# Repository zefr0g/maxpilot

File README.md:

# MaxPilot

> Pilotez vos radiateurs électriques en WiFi depuis Home Assistant — carte open-source, ~12 € de composants, 100 % local.

[English version → README.en.md](README.en.md)

| Carte assemblée | Boîtier imprimé en 3D |
|:--:|:--:|
|  |  |

MaxPilot est une carte open-source qui se branche sur le **fil pilote** de vos radiateurs électriques et commande leur mode (Confort, Éco, Hors-gel, Arrêt) depuis Home Assistant, via ESPHome. Plus besoin de programmateur mural : la carte remplace le thermostat central, sans cloud ni abonnement. Elle est conçue autour de composants **peu coûteux et faciles à trouver** (WeMos D1 Mini, optocoupleurs, alimentation HLK-PM01) et se soude entièrement en traversant : accessible à tout amateur d'électronique.

## Pourquoi MaxPilot ?

- **Local et ouvert** — pas de cloud, pas d'application propriétaire : ESPHome + Home Assistant, et vous gardez le contrôle
- **Vraiment pas cher** — ~12 € par radiateur, tout compris (voir [le coût](#coût))
- **Un fil pilote, plusieurs radiateurs** — une carte pilote tous les radiateurs raccordés au même fil pilote
- **Thermostat intégré** — importez n'importe quel capteur de température de Home Assistant et laissez la carte réguler
- **Conçu pour le 230 V** — fusible, varistance, alimentation isolée, distances d'isolement IPC-2221B / IEC 62368-1, boîtier fermé
- **Tout est fourni** — schéma et PCB KiCad, Gerbers, nomenclature, firmware, boîtier OpenSCAD/STL

| | MaxPilot | Module WiFi du commerce (ex. Heatzy Pilote) | Module Z-Wave (ex. Qubino Fil Pilote) |
|---|:--:|:--:|:--:|
| Prix indicatif par radiateur | **~12 €** | ~50 € | ~60 € |
| Fonctionne sans cloud | ✅ | ❌ | ✅ |
| Intégration Home Assistant | native (ESPHome) | via intégration tierce | via Z-Wave JS + clé USB |
| Firmware modifiable | ✅ | ❌ | ❌ |
| Matériel ouvert | ✅ | ❌ | ❌ |
| Montage à faire soi-même | oui (soudure traversante) | non | non |

---

## Sommaire

- [C'est quoi le fil pilote ?](#cest-quoi-le-fil-pilote-)
- [Fonctionnalités](#fonctionnalités)
- [Coût](#coût)
- [Démarrage rapide](#démarrage-rapide)
- [Câblage](#câblage)
- [Schéma](#schéma)
- [Nomenclature](#nomenclature)
- [Firmware ESPHome](#firmware-esphome)
- [Intégration Home Assistant](#intégration-home-assistant)
- [Fabrication du PCB](#fabrication-du-pcb)
- [Boîtier](#boîtier)
- [Sécurité](#sécurité)
- [Contribuer](#contribuer)
- [Licence](#licence)

---

## C'est quoi le fil pilote ?

Le **fil pilote** est le système normalisé en France (protocole GIFAM) pour piloter les radiateurs électriques. En plus de la phase et du neutre, un fil supplémentaire — le fil pilote — transporte un signal de commande dérivé du 230 V. Le radiateur choisit son mode selon la **forme du signal** qu'il reçoit :

| Mode | Ce que fait le radiateur | Signal sur le fil pilote | SSR1 | SSR2 |
|---|---|---|:---:|:---:|
| **Confort** | Chauffe à la température du thermostat | Pas de signal (fil ouvert) | OFF | OFF |
| **Éco** | Réduit la consigne de ~3-4 °C | Sinusoïde complète 230 V | ON | ON |
| **Hors-gel** | Maintient ~7 °C minimum | Alternance négative uniquement | ON | OFF |
| **Arrêt** | Radiateur éteint | Alternance positive uniquement | OFF | ON |

```
Confort (pas de signal)            Éco (sinusoïde complète)

                                        ╭──╮      ╭──╮
                                       ╱    ╲    ╱    ╲
 ──────────────────────        ───────╱──────╲──╱──────╲───
                                    ╲    ╱    ╲    ╱
                                     ╰──╯      ╰──╯

   SSR1: OFF  SSR2: OFF           SSR1: ON   SSR2: ON

Hors-gel (alternance −)            Arrêt (alternance +)

                                        ╭──╮      ╭──╮
                                       ╱    ╲    ╱    ╲
 ───────────────────────────       ────╱──────╲──╱──────╲───
    ╲    ╱    ╲    ╱
     ╰──╯      ╰──╯

   SSR1: ON   SSR2: OFF           SSR1: OFF  SSR2: ON
```

MaxPilot utilise **deux optocoupleurs triac MOC3041M** (SSR1 et SSR2), chacun en série avec une **diode 1N4007** montée en sens opposé. SSR1 laisse passer l'alternance négative, SSR2 l'alternance positive ; les deux ensemble donnent la sinusoïde complète. Les MOC3041M commutent au passage par zéro, donc sans parasites. Le fil pilote ne consomme que quelques milliampères : une seule carte peut piloter **tous les radiateurs raccordés au même fil pilote**.

---

## Fonctionnalités

- ESP8266 (WeMos D1 Mini) avec WiFi intégré, firmware ESPHome
- Sélecteur de mode Confort / Éco / Hors-gel / Arrêt dans Home Assistant
- Thermostat optionnel : capteur de température importé depuis Home Assistant, presets Confort / Éco / Hors-gel / Absent
- Mode restauré après coupure de courant
- Alimentation AC/DC isolée (HLK-PM01, 5 V), fusible 1 A, varistance 275 V
- Optocoupleurs à passage par zéro (MOC3041M)
- PCB 99 × 38 mm, composants traversants uniquement, 4 trous de fixation M2
- Boîtier imprimable en 3D (OpenSCAD + STL) avec aération au-dessus de l'alimentation

---

## Coût

Prix indicatifs 2026 (AliExpress / LCSC / grossistes, hors port), pour une carte :

| Composant | Prix approx. |
|---|--:|
| WeMos D1 Mini | 3,00 € |
| HLK-PM01 | 3,00 € |
| 2 × MOC3041M | 1,20 € |
| Bornier 7,62 mm | 0,70 € |
| Porte-fusible + fusible 1 A | 0,80 € |
| Varistance, diodes, résistances, condensateur | 0,60 € |
| PCB (JLCPCB, lot de 5) | ~2,00 € |
| **Total** | **~11 €** |

---

## Démarrage rapide

1. **Commander le PCB** — envoyez `hardware/gerber/MaxPilot.zip` à JLCPCB, PCBWay, Aisler…
2. **Souder les composants** — voir la [nomenclature](#nomenclature) ; tout est traversant
3. **Flasher le firmware** — branchez le D1 Mini en USB et lancez `esphome run esphome/maxpilot_ch1.yaml` (voir [Firmware ESPHome](#firmware-esphome))
4. **Câbler la carte** — phase, neutre et fil pilote sur le bornier, courant coupé (voir [câblage](#câblage))
5. **Fermer le boîtier** — indispensable, la carte est au 230 V
6. **Ajouter à Home Assistant** — le périphérique est détecté automatiquement par l'intégration ESPHome
7. **Piloter vos radiateurs** — depuis le tableau de bord, des automatisations ou le thermostat

---

## Câblage

> ⚠️ **ATTENTION** : coupez le courant au disjoncteur avant tout câblage et vérifiez l'absence de tension.

La carte se branche sur le bornier 3 points (J1). Le fil pilote de votre radiateur est le fil noir (parfois gris) qui sort du radiateur à côté de la phase et du neutre. Il ne doit **jamais** être raccordé au neutre ni à la terre.

```
                    Bornier J1
                   ┌─────┬─────┬─────┐
                   │  L  │  N  │  P  │
                   └──┬──┴──┬──┴──┬──┘
                      │     │     │
                      │     │     └──── Fil pilote vers le(s) radiateur(s)
                      │     │
                      │     └────────── Neutre (bleu)
                      │
                      └──────────────── Phase (marron ou rouge)

          Depuis le tableau électrique (circuit des radiateurs)
```

Alimentez la carte depuis le **même circuit** que les radiateurs qu'elle pilote : le signal fil pilote est référencé au neutre du radiateur.

---

## Schéma

Le schéma complet est dans `hardware/kicad/MaxPilot.kicad_sch` (KiCad 9).

### Architecture

```
Secteur ──► F1 (fusible 1 A) ──► RV1 (varistance) ──► PS1 (HLK-PM01) ──► 5 V
   │                                                          │
   │                                                   U1 (WeMos D1 Mini)
   │                                                    │            │
   │                                                GPIO D3      GPIO D7
   │                                                    │            │
   │                                                R1 (570 Ω)   R2 (570 Ω)
   │                                                    │            │
   ├──────────────────────────────────────────── U2 (MOC3041M)  U3 (MOC3041M)
   │  phase                                            │            │
   │                                               D1 (1N4007)  D2 (1N4007)
   │                                               alternance −  alternance +
   │                                                    └─────┬──────┘
   │                                                          ▼
   └───────────────────────────────────────────────►  P (fil pilote)
```

Les deux optocoupleurs sont branchés en parallèle entre la phase et le fil pilote, chacun à travers sa diode. La partie basse tension (5 V, ESP8266) est isolée du secteur par l'alimentation HLK-PM01 et par les optocoupleurs.

### Brochage

| GPIO | Fonction |
|------|----------|
| D3 (GPIO0)  | SSR1 — U2 + D1, alternance négative (Hors-gel, Éco) |
| D7 (GPIO13) | SSR2 — U3 + D2, alternance positive (Arrêt, Éco) |

Les GPIO commandent la LED des optocoupleurs en logique inversée (niveau bas = allumé). D3 étant une broche de démarrage de l'ESP8266, elle reste haute au boot : le radiateur n'est jamais commuté pendant le démarrage.

---

## Nomenclature

| Réf | Qté | Valeur | Description |
|-----|:---:|--------|-------------|
| U1 | 1 | WeMos D1 Mini | Microcontrôleur ESP8266 |
| PS1 | 1 | HLK-PM01 | Alimentation AC/DC 5 V isolée |
| U2, U3 | 2 | MOC3041M | Optocoupleur triac à passage par zéro, DIP-6 — **couper la broche 5 avant soudure** |
| D1, D2 | 2 | 1N4007 | Diodes de sélection d'alternance |
| R1, R2 | 2 | 560–570 Ω | Résistances axiales (limitation LED des optos) |
| C1 | 1 | 22 µF 25 V | Condensateur céramique de découplage 5 V |
| F1 | 1 | 1 A | Fusible lame mini + porte-fusible Keystone 3568 |
| RV1 | 1 | 14D431K | Varistance 275 V AC |
| J1 | 1 | 3 pts, pas 7,62 mm | Bornier à vis, ex. Würth 691311400103, Phoenix MKDS 1,5/3-7,62 |

La nomenclature exportée de KiCad est dans `hardware/MaxPilot.csv`.

---

## Firmware ESPHome

Le firmware est une configuration ESPHome pure, sans code custom.

```
esphome/
├── maxpilot_ch1.yaml                   # une carte = un fichier (nom, broches, secrets)
├── maxpilot_ch1_with_temp.yaml.example # variante avec thermostat
├── secrets.yaml.example
└── common/
    ├── core.yaml             # carte, API, OTA, WiFi de secours, diagnostics
    ├── maxpilot.yaml         # logique fil pilote (SSR + sélecteur de mode)
    └── maxpilot_climate.yaml # thermostat optionnel
```

### 1. Secrets

```bash
cp esphome/secrets.yaml.example esphome/secrets.yaml
# Éditez esphome/secrets.yaml : WiFi et clé de chiffrement API (openssl rand -base64 32)
```

### 2. Flasher

```bash
# Premier flash (D1 Mini branché en USB)
esphome run esphome/maxpilot_ch1.yaml

# Mises à jour suivantes en OTA
esphome run esphome/maxpilot_ch1.yaml --device maxpilot-ch1.local
```

Pour une deuxième carte, copiez `maxpilot_ch1.yaml` et changez `name` et `ch_name`.

### 3. Thermostat (optionnel)

Si un capteur de température de la pièce existe dans Home Assistant (Zigbee, BLE, autre ESPHome…), la carte peut réguler elle-même. Voir `esphome/maxpilot_ch1_with_temp.yaml.example` :

```yaml
substitutions:
  temp_sensor_entity: "sensor.temperature_salon"   # votre capteur dans Home Assistant

packages:
  core: !include common/core.yaml
  maxpilot: !include common/maxpilot.yaml
  climate: !include common/maxpilot_climate.yaml
```

| Preset | Consigne | Fil pilote |
|--------|:--------:|-----------------|
| **Confort** | 19 °C | Confort quand il fait froid, Éco une fois la consigne atteinte |
| **Éco** | 17 °C | idem, autour de 17 °C |
| **Hors-gel** | 7 °C | idem, autour de 7 °C |
| **Absent** | — | Arrêt |

Le thermostat agit toujours à travers le sélecteur de mode : l'état affiché dans Home Assistant est celui réellement envoyé au radiateur.

### 4. Adoption depuis le tableau de bord ESPHome

La configuration déclare `dashboard_import` : une carte déjà flashée peut être adoptée en un clic depuis le tableau de bord ESPHome (« Adopt »), qui récupère la configuration directement depuis ce dépôt.

---

## Intégration Home Assistant

Une fois flashée, MaxPilot est découverte automatiquement par l'intégration ESPHome. Vous trouverez :

- **Fil Pilote CH1** — sélecteur de mode : Confort, Éco, Hors-gel, Arrêt
- **Radiateur CH1** *(si thermostat activé)* — entité climate avec consigne et presets
- Signal WiFi, uptime et version dans les diagnostics

Exemple d'automatisation :

```yaml
automation:
  - alias: "Radiateurs - Éco la nuit"
    triggers:
      - trigger: time
        at: "22:00:00"
    actions:
      - action: select.select_option
        target:
          entity_id: select.maxpilot_ch1_fil_pilote_ch1
        data:
          option: "Éco"
```

---

## Fabrication du PCB

Fichiers Gerber prêts pour JLCPCB, PCBWay, Aisler… dans `hardware/gerber/` (`MaxPilot.zip` contient tout). PCB 2 couches, 1,6 mm, 99 × 38 mm ; les options par défaut du fabricant conviennent.

| Face avant | Face arrière |
|:--:|:--:|
|  |  |

---

## Boîtier

Un boîtier imprimable en 3D est fourni dans `hardware/enclosure/` (source OpenSCAD + STL). Imprimez en PLA ou PETG, sans supports, face ouverte vers le haut. Le couvercle comporte des fentes d'aération au-dessus de l'alimentation et une découpe pour les fils côté bornier.

- **Vis PCB** : 4 × M2×6 (auto-taraudantes dans les plots)
- **Vis couvercle** : 4 × M3×13 (auto-taraudantes dans les piliers d'angle)

---

## Sécurité

> ⚠️ **ATTENTION : ce projet manipule la tension secteur (230 V AC). Risque d'électrocution mortelle.**
> Coupez toujours le courant avant toute intervention. La carte doit être installée dans un boîtier fermé, hors de portée. Vous êtes responsable de la conformité de votre installation.

Le PCB v2.0 respecte les distances d'isolement IPC-2221B et IEC 62368-1 :
- Clearance secteur ↔ basse tension : ≥ 3,0 mm
- Ligne de fuite (*creepage*) : ≥ 5,0 mm
- Pistes secteur sur la face arrière uniquement, sans via

---

## Contribuer

Photos de montage, retours sur des modèles de radiateurs, corrections et améliorations sont les bienvenus. Voir [CONTRIBUTING.md](CONTRIBUTING.md). Les questions sont ouvertes dans les [Discussions](https://github.com/zefr0g/maxpilot/discussions).

Si ce projet vous est utile, une ⭐ sur le dépôt aide d'autres personnes à le trouver.

---

## Changelog

### v2.1
- Firmware : adoption depuis le tableau de bord ESPHome, thermostat piloté via le sélecteur, secrets uniquement dans le fichier de la carte
- Boîtier v2.4 : piliers de couvercle dans les angles, insertion du PCB sans inclinaison, fentes d'aération
- Documentation : polarité des alternances corrigée (Hors-gel = négative, Arrêt = positive), coût, comparatif
- CI GitHub Actions : validation ESPHome et DRC KiCad

### v2.0
- Distances d'isolement conformes IPC-2221B / IEC 62368-1
- Bornier J1 remplacé par pas 7,62 mm
- Empreinte MOC3041M corrigée (pin 5 NPTH)
- Routage secteur sur face arrière (B.Cu), sans vias
- Trous de fixation M2 aux 4 coins
- Boîtier imprimable en 3D (hardware/enclosure/)

### v1.0
- Premier design fonctionnel

---

## Licence

CERN Open Hardware Licence Version 2 — Strongly Reciprocal (CERN-OHL-S-2.0)

Voir [LICENSE](LICENSE) pour le texte complet.

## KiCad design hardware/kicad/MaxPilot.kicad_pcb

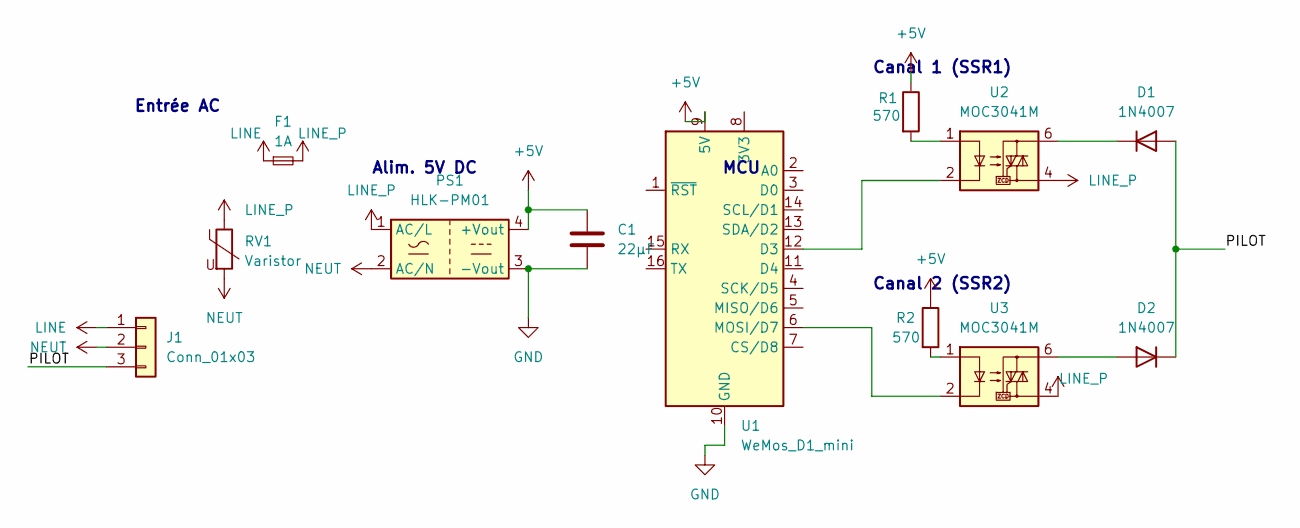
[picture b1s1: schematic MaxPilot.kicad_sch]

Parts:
C1: 22µF; C_Disc_D8.0mm_W2.5mm_P5.00mm
D1, D2: 1N4007; D_DO-41_SOD81_P10.16mm_Horizontal
F1: 1A; R_Axial_DIN0411_L9.9mm_D3.6mm_P15.24mm_Horizontal
J1: Conn_01x03; TerminalBlock_Generic_1x03_P7.62mm_Horizontal
PS1: HLK-PM01; Converter_ACDC_HiLink_HLK-PMxx
R1, R2: 570; R_Axial_DIN0207_L6.3mm_D2.5mm_P10.16mm_Horizontal
RV1: Varistor; RV_Disc_D12mm_W4.5mm_P7.5mm
U1: WeMos_D1_mini; WEMOS_D1_mini_light
U2, U3: MOC3041M; MOC3041M_DIP6_W7.62mm_NC5

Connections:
+5V: C1.1, PS1.4 (+Vout), R1.1, R2.1, U1.9 (5V)
/PILOT: D1.2 (A), D2.1 (K), J1.3
GND: C1.2, PS1.3 (-Vout), U1.10 (GND)
LINE: F1.1, J1.1
LINE_P: F1.2, PS1.1 (AC/L), RV1.1, U2.4, U3.4
NEUT: J1.2, PS1.2 (AC/N), RV1.2
unnamed: D1.1 (K), U2.6
unnamed: D2.2 (A), U3.6
unnamed: R1.2, U2.1
unnamed: R2.2, U3.1
unnamed: U1.12 (D3), U2.2
unnamed: U1.6 (MOSI/D7), U3.2

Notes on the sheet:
Entrée AC
Alim. 5V DC
Canal 1 (SSR1)
Canal 2 (SSR2)
MCU

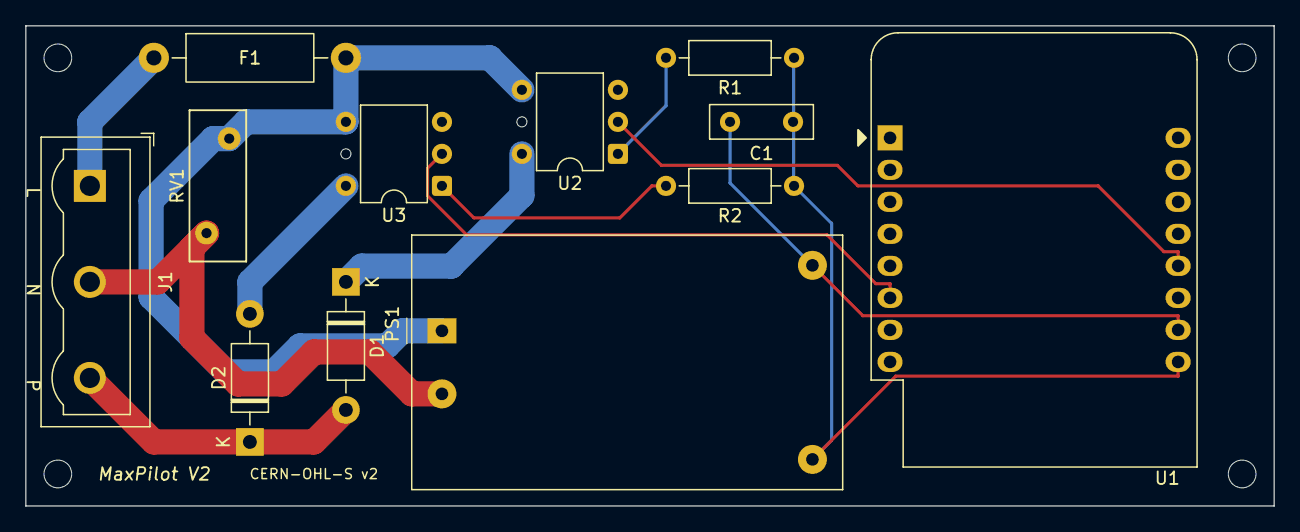
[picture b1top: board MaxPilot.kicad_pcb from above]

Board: 2 copper layers, 99.1 x 38.1 mm, 16 parts (0 on the bottom side), 12 nets.

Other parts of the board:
H1, H2, H3, H4: MountingHole_2.2mm_M2

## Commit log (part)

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2026-02-20 Initial commit: MaxPilot fil pilote radiator controller
    Open-source KiCad project for a 2-channel "fil pilote" radiator
    controller based on ESP D1 Mini (ESP8266) with ESPHome.
    Includes schematic, PCB layout, Gerber manufacturing files,
    BOM, ESPHome configuration example, and bilingual documentation.
    Licensed under CERN-OHL-S-2.0.
2026-02-20 Add fil pilote protocol explanation and ESPHome common configs
    Add detailed bilingual description of the fil pilote protocol with
    waveform diagrams and SSR state table for each mode (Confort, Éco,
    Hors-gel, Arrêt). Include common/ ESPHome configuration files.
2026-02-20 Improve README for non-technical users, add board photo
    Add plain-language intro, quick start guide, wiring diagram,
    Home Assistant integration with example automations, and
    practical mode descriptions. Include assembled board photo.
2026-02-20 Add v2 improvements section, specify BOM component values
    Specify C1 as 22µF 25V ceramic and RV1 as MOV 275V (14D431K).
    Add bilingual "Possible Improvements (v2)" section documenting
    fuse sizing, output protection, and creepage distance considerations.
2026-02-20 Add DRC findings to v2 improvements section
    Document specific clearance violations found by DRC: NEUT trace
    0.44mm from D1 pad (IPC requires >2.5mm for 230V), J1 terminal
    block pad spacing insufficient, and unconnected traces on U3/R2.
2026-02-20 Revamp ESPHome config: select entity + optional temp sensor
    Replace raw SSR switches with a single "Fil Pilote" select entity
    (Confort/Éco/Hors-gel/Arrêt). SSRs are now internal. Add optional
    room temperature sensor imported from Home Assistant via substitution.
    Include example config with temperature sensor enabled.
2026-02-20 Add optional thermostat climate control with temperature presets
    When a room temperature sensor is configured, a climate entity can be
    added to automatically switch between Confort/Éco based on room
    temperature. Includes Confort (19°C), Éco (17°C), Hors-gel (7°C)
    and Absent presets.
2026-02-20 Move KiCad and Gerber files to hardware/ directory
    Organize project structure:
    - hardware/kicad/ — KiCad schematic, PCB and project files
    - hardware/gerber/ — manufacturing Gerber and drill files
    - hardware/ — BOM and component placement files
2026-02-20 Move ESPHome files to esphome/ directory
    Reorganize project structure by moving all ESPHome configuration
    files into a dedicated esphome/ subdirectory. Update README paths.
2026-02-20 Highlight low-cost components in README description
2026-02-21 Add safety DRC rules for 230V mains (v2 prep)
    Create MaxPilot.kicad_dru with IPC-2221B / IEC 62368-1 compliant
    constraints:
    - Mains-to-LV clearance: 3.0 mm minimum
    - Mains-to-LV creepage: 5.0 mm minimum
    - Mains internal clearance (LINE/NEUT/PILOT): 2.5 mm minimum
    (flags J1 5.08 mm pitch → 7.62 mm pitch required)
2026-02-21 Add local footprint library with 3-pin 7.62mm terminal block
    - MaxPilot.pretty/TerminalBlock_Generic_1x03_P7.62mm_Horizontal.kicad_mod
    Derived from Wuerth 691311400102 (2-pin), extended to 3 pins.
    Pad-to-pad edge gap = 7.62 - 2.54 = 5.08mm (passes 2.5mm clearance rule).
    - fp-lib-table: registers MaxPilot.pretty as project-local footprint library
    To use in PCB editor: right-click J1 → Change Footprint →
    select MaxPilot:TerminalBlock_Generic_1x03_P7.62mm_Horizontal
2026-02-21 Fix footprint: remove invalid semicolon comments
    KiCad S-expression parser does not support ; comments.
2026-02-21 Add Net-(D2-Pad2) to Line net class
    This net carries fused mains live voltage (AC/L input to PS1,
    fuse output to optocoupler TRIAC outputs) and must be treated
    as mains, not LV. Fixes 9 false DRC violations where it was
    being compared against NEUT with the Mains_to_LV rules.
2026-02-21 Exclude same-footprint violations from mains DRC rules
    MOC3041M (U2/U3) has NC pin 5 between its two mains pins (4/6)
    and only 7.62mm between LV and mains pin rows — the component
    handles isolation internally. Exclude intra-footprint violations
    with A.Parent != B.Parent condition.
2026-02-21 Add LINE_P and Net-(D2-Pad2) to Line net class
    LINE_P is the fuse-protected mains live net and must be treated
    as mains voltage (2mm traces, 3mm/5mm clearance/creepage rules).
    Also restores Net-(D2-Pad2) which KiCad dropped on file save.
2026-02-21 Add MOC3041M NC pad 5 to Line net class
    Pin 5 of MOC3041M is the substrate/NC pin on the mains (TRIAC)
    side, physically between pins 4 and 6 which are both mains.
    Wildcard pattern *NC-Pad5* matches unconnected-(U2-NC-Pad5)
    and unconnected-(U3-NC-Pad5), resolving 6 false DRC violations.
2026-02-21 Restore Line clearance to 3.0mm; add MOC3041M NC-Pad5 nets
    - Line net class clearance: 0.5mm → 3.0mm (KiCad had reset it)
    FreeRouting uses net class clearance, so this is critical for
    correct autorouting between mains nets.
    - Add unconnected-(U2-NC-Pad5) and unconnected-(U3-NC-Pad5) to
    Line class: pin 5 is the mains-side substrate of MOC3041M,
    physically between mains pins 4 and 6.
2026-02-21 Set Line net class clearance to 2.5mm for FreeRouting
    FreeRouting uses net class clearance for routing, not DRU rules.
    3.0mm between all mains nets was too tight to route.
    2.5mm is the IPC-2221B minimum between mains conductors themselves.
    The DRU Mains_to_LV_Clearance rule (3.0mm) still enforces correct
    separation between mains and LV nets at DRC time — any remaining
    mains-to-LV violations after autorouting need manual correction.
2026-02-21 PCB v2.0: redesign for IPC-2221B/IEC 62368-1 mains safety compliance
    - Replace J1 terminal block with 7.62mm pitch (was 5.08mm)
    - Add IPC-2221B/IEC 62368-1 DRC rules (clearance ≥3.0mm mains↔LV,
    ≥2.5mm mains↔mains, creepage ≥5.0mm) in MaxPilot.kicad_dru
    - Add MOC3041M_DIP6_W7.62mm_NC5 footprint: pin 5 (TRIAC substrate,
    DO NOT CONNECT) replaced with NPTH mechanical hole
    - Assign mains nets to Line netclass (LINE, NEUT, LINE_P,
2026-02-21 Update PCB render images for v2.0 layout
2026-02-21 Regenerate Gerber files for v2.0 PCB layout
2026-02-21 Add CERN-OHL-S v2 license text to PCB back silkscreen
2026-02-21 Move CERN-OHL-S v2 license to front silkscreen; regenerate Gerbers and images
2026-02-21 Add M2 mounting holes, reroute PCB, add 3D printable enclosure
    - Add 4× M2 mounting holes at corners (H1-H4, annotated)
    - Reroute PCB after component repositioning; DRC clean (9 warnings, 0 errors)
    - Add hardware/enclosure/MaxPilot_box.scad: OpenSCAD parametric enclosure
    - Base with 4× M2 boss standoffs, friction-fit lid, J1 wire entry cutout
    - Box exterior ~107 × 46 × 36.6 mm, assembly with 4× M2×6 self-tapping screws
    - Regenerate Gerbers and PCB images for updated layout
2026-02-21 Fix PCB SVG exports: remove title block/drawing sheet legend
    Add --exclude-drawing-sheet to kicad-cli export to remove the KiCad
    frame (grid labels A/B/1/2, Date, Rev, Title, Size fields) from SVGs.
2026-02-21 Fix enclosure CSG: bosses now correctly survive interior subtraction
    Boss cylinders were being fully removed by the interior cavity difference
    because they shared the same z-start (floor_t). Fix: separate into
    union(hollow_shell, bosses_with_holes) so bosses are added after the
    interior subtraction. Also add part variable for STL export, export
    MaxPilot_base.stl and MaxPilot_lid.stl.
    Base: 535 facets (was 15). Lid: 16 facets (rectangular, no curves).
2026-02-21 Add rounded exterior corners to enclosure (corner_r = 3 mm)
    Use hull() of corner cylinders for vertical edge rounding on base and lid.
    Add corner_r parameter and rounded_rect() helper module. Regenerate STLs.
2026-02-21 Fix lid STL print orientation: outer face at z=0, lip points up
    Lid was exported with lip at negative z, causing it to appear underground
    in FreeCAD/slicers. Apply flip transform when part="lid" so the flat outer
    face sits on the build plate and the friction-fit lip points upward.
    Preview (part="both") keeps the design orientation unchanged.
2026-02-21 Add M3 corner ear tabs to secure lid to base
    Tight interior (1 mm PCB clearance) leaves no room for internal posts,
    so 4 external ear tabs protrude from the rounded corners. Each ear is a
    5 mm-radius cylinder hulled to the existing corner, offset 3 mm outward
    along the diagonal.
    - Base: ear boss full height, 2.5 mm pilot hole 10 mm deep (M3 self-tapping)
    - Lid: matching ear extension (lid_t thick), 3.3 mm clearance hole,
2026-02-21 Fix PCB bosses removed by ear-tab interior re-subtraction
    The outer difference() used to keep ear hulls out of the interior was
    also subtracting the PCB standoff bosses. Move bosses to the outer
    union() so they are added after the interior re-subtraction.
    Base: 979 facets (was 459 with missing bosses, 535 with bosses only).
2026-02-21 Engrave 'MaxPilot' text on lid outer face (0.5 mm deep)
2026-02-21 Update DRC report after reroute fix; PCB clean (9 warnings, 0 errors)
    All 9 remaining violations are expected lib_footprint_mismatch warnings
    for custom/offline footprints (MOC3041M_NC5, HLK-PMxx, WEMOS_D1_mini).
    0 unconnected pads, 0 clearance errors.
2026-02-21 Split bilingual README into FR (README.md) and EN (README.en.md)
    Each file is now monolingual with a link to the other at the top.
    Also fixes Gerber drill file list (MaxPilot.drl, unified PTH+NPTH)
    and adds v2.0 changelog entries (B.Cu mains routing, M2 holes, enclosure).
2026-02-21 Add L/N/P silkscreen labels on J1 terminal block
2026-02-21 Improve schematic readability
    - Fix 2 diagonal wires in PS1 DC output area (now orthogonal: vertical
    down from +5V symbol then horizontal to C1 top pin)
    - Move +5V power symbol to standard orientation (rot=0, directly above
    PS1 +Vout pin)
    - Add bold section labels: Entrée AC, Alim. 5V DC, MCU, Canal 1 (SSR1),
    Canal 2 (SSR2)
2026-02-21 Fix BOM CSV: add missing RV1, correct J1 pitch and U2/U3 footprint
    - Add missing RV1 (275V MOV varistor) — was in schematic/PCB but omitted
    - Fix J1 terminal block footprint: 5.08mm → 7.62mm pitch
    - Fix U2/U3 footprint: generic DIP-6 → MOC3041M_DIP6_W7.62mm_NC5 with
    note about pin 5 NPTH (must clip before soldering)
2026-02-21 Redesign lid attachment: internal conical pillars instead of ear tabs
    Replace external M3 corner ear tabs with 4 internal conical pillars:
    - Each pillar is dual-purpose: M2 boss at base (PCB standoff, same as
    before) + tapered cone (boss_d=5.5 → pillar_top_d=4.5 mm) reaching
    the box rim + M3×10 blind pilot hole at tip for lid screw
    - Lid is now a flat plate (no friction-fit lip) held by 4× M3×13
    pan-head self-tapping screws — simpler, more rigid than press-fit
2026-02-21 Enclosure: thinner walls, fused pillars, smaller wire cutout
    - wall 3→2.5 mm, gap 1→1.5 mm (same exterior footprint, more interior room)
    - Cone orientation corrected: wide at rim, tapering down
    - Top pillars fused into corner walls via hull() at rim level
    - J1 wire cutout reduced 14.6→7.6 mm tall, raised to wire-entry height
2026-02-21 README: badges, tagline, BOM cleanup, enclosure section
    - Add shields.io badges (license, ESPHome, KiCad 9, Home Assistant)
    - Add one-line tagline as blockquote
    - Remove KiCad footprint column from BOM tables
    - Fix EN architecture diagram labels (were in French)
    - Add dedicated Enclosure section with screw specs
    - Improve Safety section formatting
2026-02-21 Enclosure v2.3: move lid pillars to corners, increase gap for straight PCB insertion
    Lid pillars moved from PCB mounting hole positions (inside PCB outline)
    to interior box corners — PCB now drops straight in, no tilt needed.
    Gap increased 1.5→6 mm so PCB footprint clears the corner pillars.
    Pillar rim 7→5 mm, foot 5→3 mm to fit within the corner zone.
    Box exterior: 116 × 55 × 33.6 mm (was 107 × 46 mm)
2026-02-22 update enclosure
2026-02-22 updated schematics page size, adjusting the box

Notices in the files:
README.md:
License: CERN-OHL-S-2.0
